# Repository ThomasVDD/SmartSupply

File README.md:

# SmartSupply
SmartSupply is a digital battery powered lab powersupply. It is Arduino compatible and can be controlled via PC over USB.

## Specifications:
 * 0 - 1A,  steps of 1 mA  (10 bit DAC)
 * 0 - 20V, steps of 20 mV (10 bit DAC) (true 0V operation)
 * Voltage measurement: 20 mV resolution (10 bit ADC)
 * Current measurement: 
      -     < 40mA:  10uA resolution (ina219)
 			< 80mA:  20uA resolution (ina219)
 			< 160mA: 40uA resolution (ina219)
			< 320mA: 80uA resolution (ina219)
			> 320mA: 1mA  resolution (10 bit ADC)

## Features: 
 * Constant voltage and constant current modes
 * Uses a low noise linear regulator, preceded by a tracking preregulator to minimize power dissipation
 * Aluminium case end panel used as heatsink 
 * Use of handsolderable components to keep the project accessible 
 * Powered by ATMEGA328P, programmed with Arduino IDE
 * PC communication via Java application over micro usb
 * Powered by 2 protected 18650 Lithium Ion cells
 * 19 mm spaced banana plugs for compatibility with BNC adapters

## Theory of operation: 

To understand the operation of the circuit, we will have to look at the schematic. I divided it into functional blocks, such that it is easier to understand; I will thus also explain the operation step by step. 

### Main block
The operation is based around the LT3080 chip: it's a linear voltage regulator, which can step down voltages, based on a control signal. This control signal will be generated by a microcontroller; how this is done, will be explained in detail later. 

#### Voltage setting
The circuitry around the LT3080 generates the appropriate control signals. First, we will take a look at how the voltage is set. 
The voltage setting from the microcontroller is a PWM signal (PWM_Vset), which is filtered by a lowpass filter (C9 & R26). This produces an analog voltage - between 0 and 5 V - proportional to the wanted output voltage. Since our output range is 0 - 20 V, we will have to amplify this signal with a factor of 4. This is done by the non inverting opamp configuration of U3C. The gain to the set pin is determined by R23//R24//R25 and R34. These resistors are 0.1% tolerant, to minimize errors. R39 and R36 don't matter here, as they are part of the feedback loop.

#### Current setting
This set pin can also be used for the second setting: current mode. We want to measure the current draw, and turn the output off when this exceeds the wanted current. Therefore, we start again by a PWM signal (PWM_Iset), generated by the microcontroller, which is now lowpass filtered and attenuated to go from a 0 - 5 V range to a 0 - 2 V range. This voltage is now compared to the voltage drop across the current sense resistor (ADC_Iout, see below) by the comparator configuration of opamp U3D. If the current is too high, this will turn on an led, and also pull the set line of the LT3080 to ground (via Q2), thus turning off the output.

The measurement of the current, and the generation of the signal ADC_Iout is done as follows. The output current flows through resistors R7 - R16. These total 1 ohm; the reason for not using 1R in the first place is twofold: 1 resistor would need to have a higher power rating (it needs to dissipate at least 1 W), and by using 10 1% resistors in parallel, we get a higher precision than with a single 1 % resistor. A good video about why this works can be found here: https://www.youtube.com/watch?v=1WAhTdWErrU&t=1s
When current flows through these resistors, it creates a voltage drop, which we can measure, and it is placed before the LT3080, since the voltage drop across it should not influence the output voltage. 
The voltage drop is measured with a differential amplifier (U3B) with a gain of 2. This results in a voltage range of 0 - 2 V (more on that later), hence the voltage divider at the PWM signal of the current. The buffer (U3A) is there to make sure that the current flowing into resistors R21, R32 and R33 is not going through the current sense resistor, which would influence it's reading. 
Also note that this should be a rail-to-rail opamp, because the input voltage at the positive input equals the supply voltage. 

The non inverting amplifier is only for the course measurement though, for very precise measurements, we have the INA219 chip on board. This chip allows us to measure very small currents, and is addressed via I2C. 

#### Additional things
At the output of the LT3080, we have some more stuff. First of all, there is a current sink (LM334). This draws a constant current of 677 uA (set by resistor R41), to stabilize the LT3080. It is however not connected to ground, but to VEE, a negative voltage. This is needed to allow the LT3080 to operate down to 0 V. When connected to ground, the lowest voltage would be about 0.7 V. This seems low enough, but keep in mind that this prevents us from turning the powersupply completely off. 
The zener diode D3 is used to clamp the output voltage if it goes above 22 V, and the resistor divider drops the output voltage range from 0 - 20 V to 0 - 2 V (ADC_Vout). 
Unfortunately, these circuits are at the output off the LT3080, which means their current will contribute to the output current we want to measure. Fortunately, these currents are constant if the voltage stays constant; so we can calibrate the current when the load is disconnected first. 

### Charge pump
The negative voltage that we mentioned before is generated by a curious little circuit: the charge pump. For it's operation, I would refer to here: https://www.youtube.com/watch?v=LtoPHevexTM&t=2s It is fed by a 50% PWM of the microcontroller (PWM)

### Boost Converter
Let's now take a look at the input voltage of our main block: Vboost. We see that it is 8 - 24V, but wait, 2 lithium cells in series gives a maximum of 8.4 V? Indeed, and that's why we need to boost the voltage, with a so called boost converter. We could always boost the voltage to 24 V, no matter what output we want; however, this would waste a lot of power in the LT3080 and things would get toasty hot! So instead of doing that, we will boost the voltage to a bit more than the output voltage. About 2.5 V higher is appropriate, to account for the voltage drop in the current sense resistor and the dropout voltage of the LT3080. 
The voltage is set by resistors on the output signal of the boost converter. To change this voltage on the fly, we use a digital potentiometer, the MCP41010, which is controlled via SPI. 

### Battery Charging
This leads us to the real input voltage: the batteries! Since we use protected cells, we simply need to put them in series and we're done! It is important to use protected cells here, to avoid overcurrent or overdischarge, and thus damaging, of the cells. 
Again, we use a voltage divider for measuring the battery voltage, and dropping it down to a usable range.
Now on to the interesting part: the charging circuitry. We use the BQ2057WSN chip for this purpose: in combination with the TIP32CG, it basically forms a linear powersupply itself. This chip charges the cells via an appropriate CV CC trajectory. Since my batteries don't have a temperature probe, this input should be tied to half the battery voltage. This concludes the voltage regulation part of the powersupply. 

### 5V regulator
The 5 V supply voltage of the arduino is made with this simple voltage regulator. It is not the most precise 5 V output however, but this will be solved below. 

### 2.048 V voltage reference
This little chip provides a very accurate 2.048 V voltage reference. This is used as a reference for the analog signals ADC_Vout, ADC_Iout, ADC_Vbatt. That's why we needed voltage dividers to bring these signals down to 2 V. 

### Microcontroller
The brain of this project is the ATMEGA328P, this is the same chip that is used in the Arduino Uno. We already went over most control signals, but there are some interesting additions nonetheless. The rotary encoders are connected to the 2 only external interrupt pins of the arduino: PD2 and PD3. This is needed for a reliable software implementation. The switches underneath use an internal pullup resistor. 
Then there is this strange voltage divider on the chip select line of the potentiometer (Pot). A voltage divider on an output, what's that good for; you might say. As mentioned before, the 5 V supply is not teribbly accurate. It would thus be good to measure this accurately, and adjust the duty cycle of the PWM signal accordingly. But since I had no more free inputs, I had to make a pin pull double duty. When the powersupply boots, this pin is first set as an input: it measures the supply rail and calibrates itself. Next, it is set as an output and it can drive the chip select line. 

### Display Driver
For the display, I wanted a commonly available - and cheap - hitachi lcd screen. They are driven by 6 pins, but since I had no pins left, I needed another solution. A shift register to the rescue! The 74HC595 allows me to use the SPI line to control the display, thus only needing 1 additional chip select line. 

### FTDI
The last part of this powersupply is the connection with the cruel, outside world. For this, we need to convert the serial signals into USB signals. This is done by an FTDI chip, which is connected to a micro USB port for easy connection.

And that's all there is to it! 

## Licensing and acknowledgements

This project would never have been possible without the help of some people, so a shootout seems appropriate.
 * This project is based on EEVBLOG's uSupply project and his Rev C schematic. So a special thanks to David L. Jones for releasing his schematics under an open source license and sharing all his knowledge.
 * A huge thanks to Johan Pattyn for producing the prototypes of this project. 
 * Also Cedric Busschots and Hans Ingelberts deserve credit for the help with troubleshooting.

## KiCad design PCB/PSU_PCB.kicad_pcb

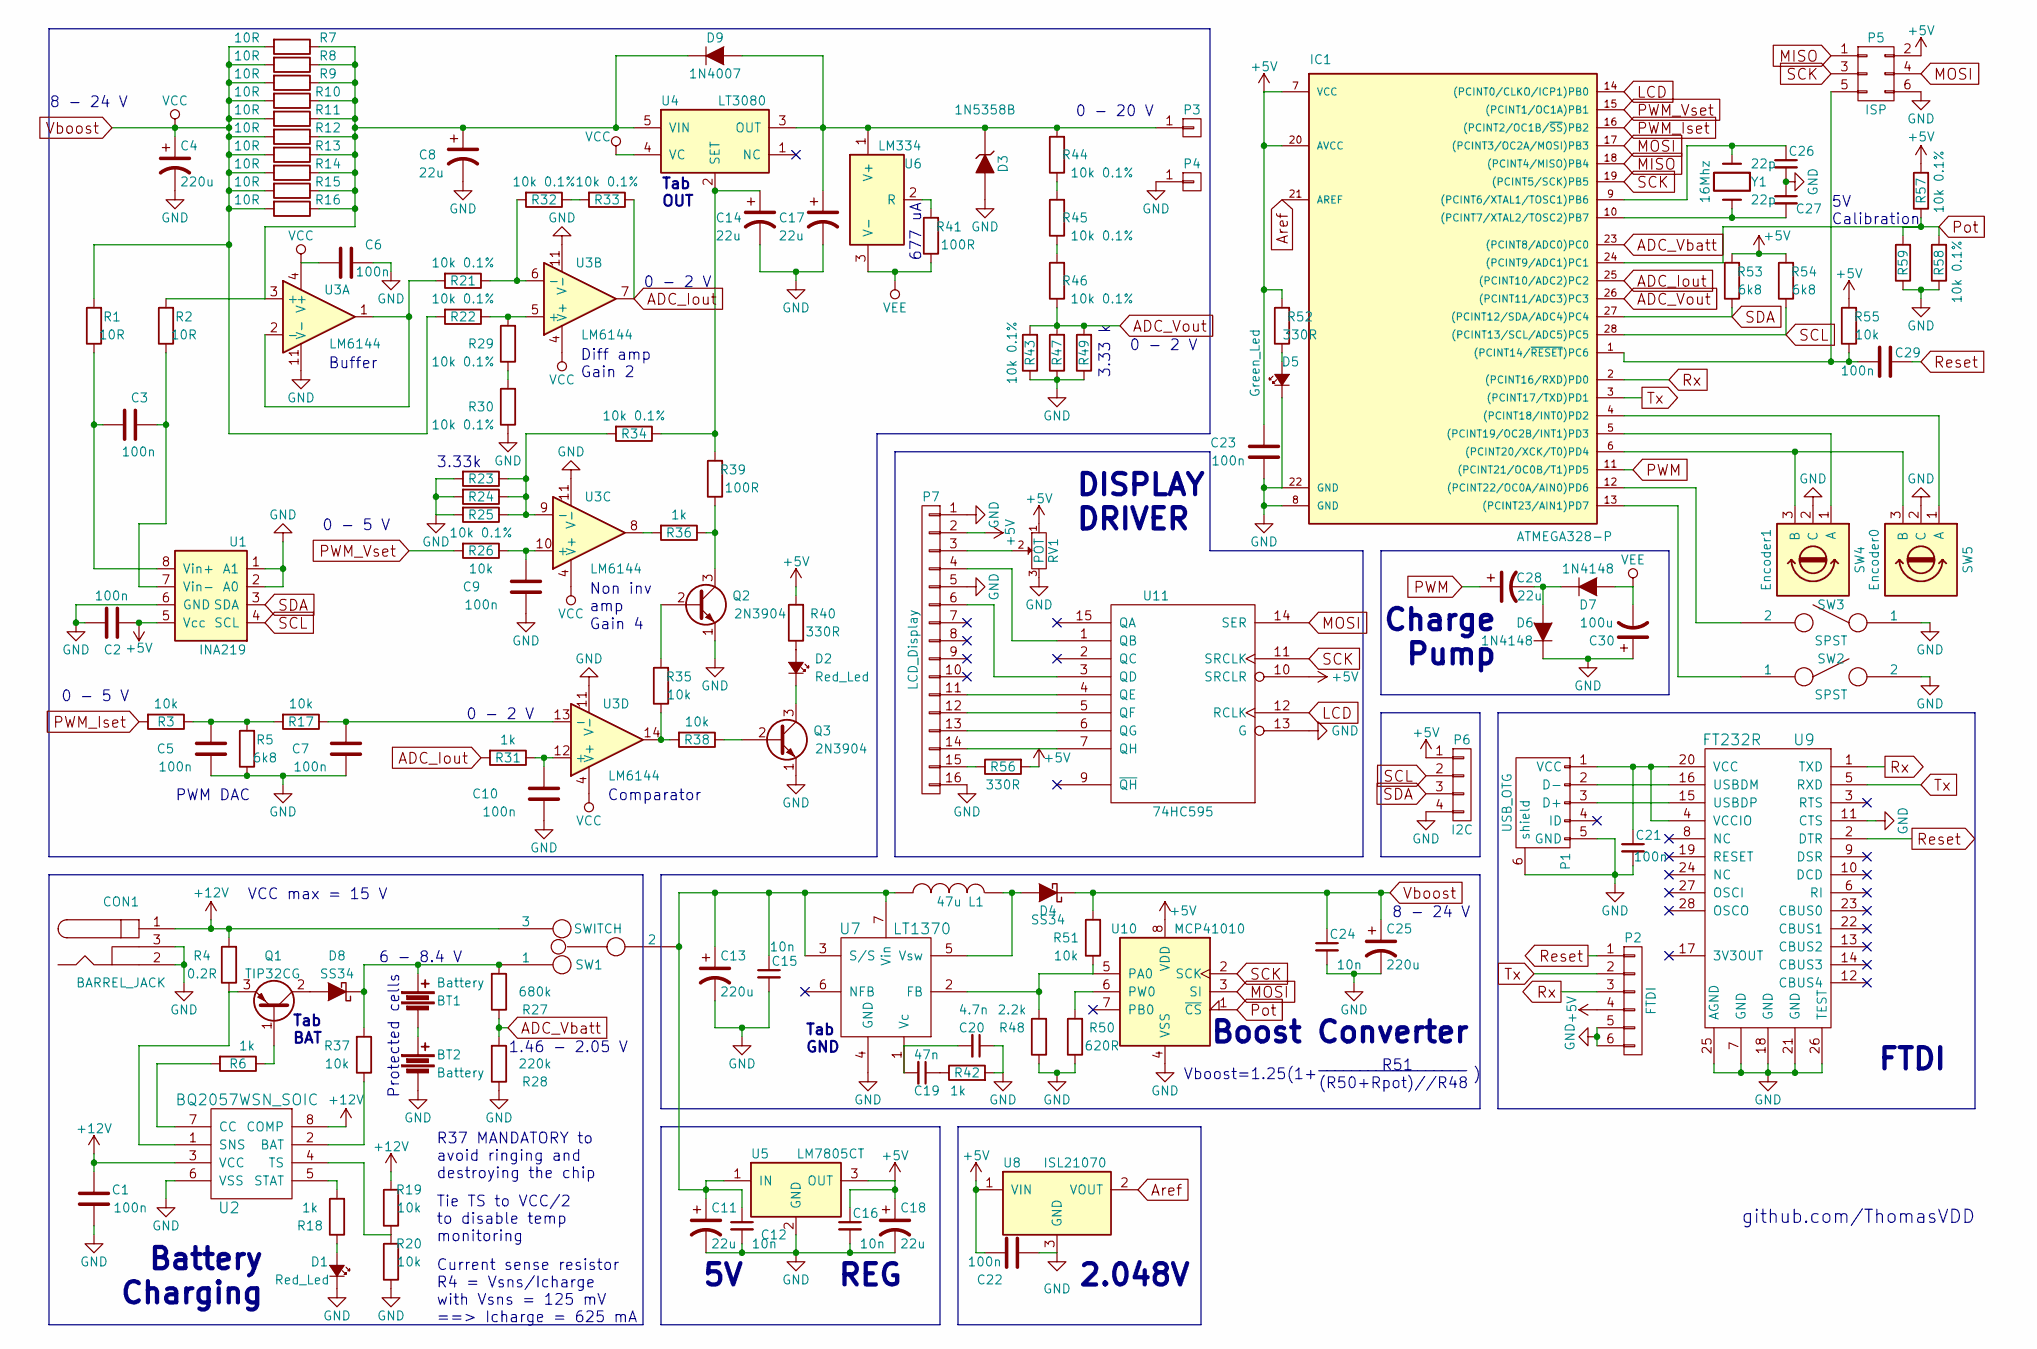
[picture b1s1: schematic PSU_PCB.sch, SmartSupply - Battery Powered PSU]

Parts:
BT1, BT2: Battery; 18650_cell
C1, C21: 100n; C_Rect_L7.0mm_W2.5mm_P5.00mm
C2, C3, C5, C6, C7, C9, C10, C22, C23, C29: 100n; C_Rect_L7_W2.5_P5
C4, C13, C25: 220u; C_Radial_D10_L13_P5
C8, C11, C14, C17, C18: 22u; C_Radial_D10_L13_P5
C12, C15, C16, C24: 10n; C_Disc_D3_P2.5
C19: 47n; C_Disc_D3.0mm_W1.6mm_P2.50mm
C20: 4.7n; C_Disc_D3.0mm_W1.6mm_P2.50mm
C26, C27: 22p; C_Disc_D3_P2.5
C28: 22u; C_Radial_D5_L11_P2.5
C30: 100u; C_Radial_D5_L11_P2.5
CON1: BARREL_JACK
D1: Red_Led; LED_D3.0mm
D2: Red_Led; LED-3MM
D3: 1N5358B; D_DO-15_P15.24mm_Horizontal
D4: SS34; SMB_Handsoldering
D5: Green_Led; LED-3MM
D6, D7: 1N4148; Diode_DO-41_SOD81_Horizontal_RM10
D8: SS34; D_SMB_Handsoldering
D9: 1N4007; D_DO-41_SOD81_P10.16mm_Horizontal
IC1: ATMEGA328-P; DIP-28_W7.62mm_LongPads
L1: 47u; SELF-WE-PD-XXL
P1: USB_OTG; Micro_usb
P2: FTDI; Pin_Header_Straight_1x06
P3: V+; 1pin
P4: V-; 1pin
P5: ISP; Pin_Header_Straight_2x03
P6: I2C; Pin_Header_Straight_1x04
P7: LCD_Display; Pin_Header_Straight_1x16
Q1: TIP32CG; TO-220_Vertical
Q2, Q3: 2N3904; TO-92_Inline_Narrow_Oval
R1, R2, R7, R8, R9, R10, R11, R12, R13, R14, R15, R16: 10R; Resistor_Horizontal_RM10mm
R3, R17, R26, R35, R38, R51, R55: 10k; Resistor_Horizontal_RM10mm
R4: 0.2R; R_0805_HandSoldering
R5, R53, R54: 6k8; Resistor_Horizontal_RM10mm
R6, R18, R42: 1k; R_Axial_DIN0207_L6.3mm_D2.5mm_P10.16mm_Horizontal
R19, R20, R37: 10k; R_Axial_DIN0207_L6.3mm_D2.5mm_P10.16mm_Horizontal
R21, R22, R25, R29, R30, R32, R33, R34, R43, R44, R45, R47: 10k 0.1%; Resistor_Horizontal_RM10mm
R23, R24, R46, R49, R57, R58, R59: 10k 0.1%; R_Axial_DIN0207_L6.3mm_D2.5mm_P10.16mm_Horizontal
R27: 680k; Resistor_Horizontal_RM10mm
R28: 220k; Resistor_Horizontal_RM10mm
R31, R36: 1k; Resistor_Horizontal_RM10mm
R39, R41: 100R; Resistor_Horizontal_RM10mm
R40, R52, R56: 330R; Resistor_Horizontal_RM10mm
R48: 2.2k; R_Axial_DIN0207_L6.3mm_D2.5mm_P10.16mm_Horizontal
R50: 620R; Resistor_Horizontal_RM10mm
RV1: POT; Potentiometer_Bourns_3296W_3-8Zoll_Inline_ScrewUp
SW1: SWITCH; SW_SPDT
SW2, SW3: SPST; SW_Tactile_SPST_Angled
SW4: Encoder1; Potentiometer_WirePads_Small
SW5: Encoder0; Potentiometer_WirePads_Small
U1: INA219; SOIC-8_3.9x4.9mm_Pitch1.27mm
U2: BQ2057WSN_SOIC; SOIC-8_3.9x4.9mm_Pitch1.27mm
U3: LM6144; DIP-14_W7.62mm_LongPads
U4: LT3080; Pentawatt_Neutral_Staggered_Verical_TO220-5-T05D
U5: LM7805CT; SOT-223-3Lead_TabPin2
U6: LM334; TO-92_Inline_Narrow_Oval
U7: LT1370; Pentawatt_Neutral_Staggered_Verical_TO220-5-T05D
U8: ISL21070; SOT-23_Handsoldering
U9: FT232R; SSOP-28_5.3x10.2mm_Pitch0.65mm
U10: MCP41010; DIP-8_W7.62mm_LongPads
U11: 74HC595; DIP-16_W7.62mm_LongPads
Y1: 16Mhz; Crystal_HC50-U_Vertical

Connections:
+5V: C2.1, C16.1, C18.1, C22.2, C23.2, IC1.7 (VCC), IC1.20 (AVCC), P2.4, P5.2, P6.1, P7.2, R40.2, R52.2, R53.2, R54.2, R55.2, R56.2, R57.2, RV1.1, U1.5 (Vcc), U5.3 (OUT), U8.1 (VIN), U10.8 (VDD), U11.10 (SRCLR), U11.16 (+5V)
+12V: C1.2, CON1.1, R4.2, R19.2, SW1.3, U2.3 (VCC), U2.8 (COMP)
ADC_Iout: IC1.25 ((PCINT10/ADC2)PC2), R31.2, R33.1, U3.7
ADC_Vbatt: IC1.23 ((PCINT8/ADC0)PC0), R27.1, R28.2
ADC_Vout: IC1.26 ((PCINT11/ADC3)PC3), R43.2, R46.1, R47.2, R49.2
Aref: IC1.21 (AREF), U8.2 (VOUT)
GND: BT2.2, C1.1, C2.2, C4.2, C5.1, C6.1, C7.1, C8.2, C9.1, C10.1, C11.2, C12.2, C13.2, C14.2, C15.2, C16.2, C17.2, C18.2, C20.1, C21.2, C22.1, C23.1, C24.2, C25.2, C26.2, C27.1, C30.1, CON1.2, CON1.3, D1.1 (K), D3.2 (A), D5.1 (K), D6.1 (K), IC1.8 (GND), IC1.22 (GND), P1.5 (GND), P1.6 (shield), P2.5, P2.6, P4.1, P5.6, P6.4, P7.1, P7.5, P7.16, Q2.1 (E), Q3.1 (E), R5.1, R20.1, R23.2, R24.2, R25.2, R28.1, R30.1, R42.2, R43.1, R47.1, R48.1, R49.1, R50.1, R58.1, R59.1, RV1.3, SW2.2, SW3.1, SW4.2 (C), SW5.2 (C), U1.1 (A1), U1.2 (A0), U1.6 (GND), U2.6 (VSS), U3.11 (V-), U5.2 (GND), U7.4 (GND), U8.3 (GND), U9.7 (GND), U9.11 (CTS), U9.18 (GND), U9.21 (GND), U9.25 (AGND), U9.26 (TEST), U10.4 (VSS), U11.8 (GND), U11.13 (G)
LCD: IC1.14 ((PCINT0/CLKO/ICP1)PB0), U11.12 (RCLK)
MISO: IC1.18 ((PCINT4/MISO)PB4), P5.1
MOSI: IC1.17 ((PCINT3/OC2A/MOSI)PB3), P5.4, U10.3 (SI), U11.14 (SER)
unnamed: BT1.1, D8.1 (K), R27.2, R37.2, SW1.1
unnamed: BT1.2, BT2.1
unnamed: C3.1, R2.1, U1.7 (Vin-)
unnamed: C3.2, R1.1, U1.8 (Vin+)
unnamed: C5.2, R3.1, R5.2, R17.2
unnamed: C7.2, R17.1, U3.13 (-)
unnamed: C8.1, D9.1 (K), R2.2, R7.1, R8.1, R9.1, R10.1, R11.1, R12.1, R13.1, R14.1, R15.1, R16.1, U3.3 (+), U4.5 (VIN)
unnamed: C9.2, R26.1, U3.10 (+)
unnamed: C10.2, R31.1, U3.12 (+)
unnamed: C11.1, C12.1, C13.1, C15.1, L1.2, SW1.2, U5.1 (IN), U7.3 (S/S), U7.7 (Vin)
unnamed: C14.1, R34.1, R39.2, U4.2 (SET)
unnamed: C17.1, D3.1 (K), D9.2 (A), P3.1, R44.2, U4.3 (OUT), U6.1 (V+)
unnamed: C19.1, R42.1
unnamed: C19.2, C20.2, U7.1 (Vc)
unnamed: C21.1, P1.1 (VCC), U9.4 (VCCIO), U9.20 (VCC)
unnamed: C26.1, IC1.9 ((PCINT6/XTAL1/TOSC1)PB6), Y1.1
unnamed: C27.2, IC1.10 ((PCINT7/XTAL2/TOSC2)PB7), Y1.2
unnamed: C28.2, D6.2 (A), D7.1 (K)
unnamed: C29.2, IC1.1 ((PCINT14/~RESET~)PC6), P5.5, R55.1
unnamed: D1.2 (A), R18.1
unnamed: D2.1 (K), Q3.3 (C)
unnamed: D2.2 (A), R40.1
unnamed: D4.2 (A), L1.1, U7.5 (Vsw)
unnamed: D5.2 (A), R52.1
unnamed: D8.2 (A), Q1.2 (C)
unnamed: IC1.4 ((PCINT18/INT0)PD2), SW5.1 (A)
unnamed: IC1.5 ((PCINT19/OC2B/INT1)PD3), SW4.1 (A)
unnamed: IC1.6 ((PCINT20/XCK/T0)PD4), SW4.3 (B), SW5.3 (B)
unnamed: IC1.12 ((PCINT22/OC0A/AIN0)PD6), SW3.2
unnamed: IC1.13 ((PCINT23/AIN1)PD7), SW2.1
unnamed: P1.2 (D-), U9.16 (USBDM)
unnamed: P1.3 (D+), U9.15 (USBDP)
unnamed: P7.3, RV1.2
unnamed: P7.4, U11.1 (QB)
unnamed: P7.6, U11.3 (QD)
unnamed: P7.11, U11.4 (QE)
unnamed: P7.12, U11.5 (QF)
unnamed: P7.13, U11.6 (QG)
unnamed: P7.14, U11.7 (QH)
unnamed: P7.15, R56.1
unnamed: Q1.1 (B), R6.1
unnamed: Q1.3 (E), R4.1, U2.1 (SNS)
unnamed: Q2.2 (B), R35.2
unnamed: Q2.3 (C), R36.1, R39.1
unnamed: Q3.2 (B), R38.1
unnamed: R6.2, U2.7 (CC)
unnamed: R18.2, U2.5 (STAT)
unnamed: R19.1, R20.2, U2.4 (TS)
unnamed: R21.1, R32.2, U3.6 (-)
unnamed: R21.2, U3.1, U3.2 (-)
unnamed: R22.1, R29.2, U3.5 (+)
unnamed: R23.1, R24.1, R25.1, R34.2, U3.9 (-)
unnamed: R29.1, R30.2
unnamed: R32.1, R33.2
unnamed: R35.1, R38.2, U3.14
unnamed: R36.2, U3.8
unnamed: R37.1, U2.2 (BAT)
unnamed: R41.2, U6.2 (R)
unnamed: R44.1, R45.2
unnamed: R45.1, R46.2
unnamed: R48.2, R51.1, U7.2 (FB), U10.5 (PA0)
unnamed: R50.2, U10.6 (PW0)
PWM: C28.1, IC1.11 ((PCINT21/OC0B/T1)PD5)
PWM_Iset: IC1.16 ((PCINT2/OC1B/~SS~)PB2), R3.2
PWM_Vset: IC1.15 ((PCINT1/OC1A)PB1), R26.2
Pot: IC1.24 ((PCINT9/ADC1)PC1), R57.1, R58.2, R59.2, U10.1 (~CS)
Reset: C29.1, P2.1, U9.2 (DTR)
Rx: IC1.2 ((PCINT16/RXD)PD0), P2.3, U9.1 (TXD)
SCK: IC1.19 ((PCINT5/SCK)PB5), P5.3, U10.2 (SCK), U11.11 (SRCLK)
SCL: IC1.28 ((PCINT13/SCL/ADC5)PC5), P6.2, R54.1, U1.4 (SCL)
SDA: IC1.27 ((PCINT12/SDA/ADC4)PC4), P6.3, R53.1, U1.3 (SDA)
Tx: IC1.3 ((PCINT17/TXD)PD1), P2.2, U9.5 (RXD)
VEE: C30.2, D7.2 (A), R41.1, U6.3 (V-)
Vboost: C4.1, C6.2, C24.1, C25.1, D4.1 (K), R1.2, R7.2, R8.2, R9.2, R10.2, R11.2, R12.2, R13.2, R14.2, R15.2, R16.2, R22.2, R51.2, U3.4 (V+), U4.4 (VC)

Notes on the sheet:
Current sense resistor R4 = Vsns/Icharge with Vsns = 125 mV ==> Icharge = 625 mA
6 - 8.4 V
1.46 - 2.05 V
677 uA
FTDI
DISPLAY DRIVER
Charge Pump
Battery Charging
Protected cells
5V REG
0 - 5 V
0 - 2 V
Buffer
Diff amp Gain 2
Comparator
PWM DAC
Non inv amp
Gain 4
3.33k
0 - 20 V
8 - 24 V
2.048V
3.33 k
8 - 24 V
Boost Converter
Tie TS to VCC/2 to disable temp monitoring
Tab GND
Tab OUT
github.com/ThomasVDD
Tab BAT
Vboost=1.25(1+ )
R51
(R50+Rpot)//R48
__________________
5V Calibration
R37 MANDATORY to avoid ringing and destroying the chip
VCC max = 15 V

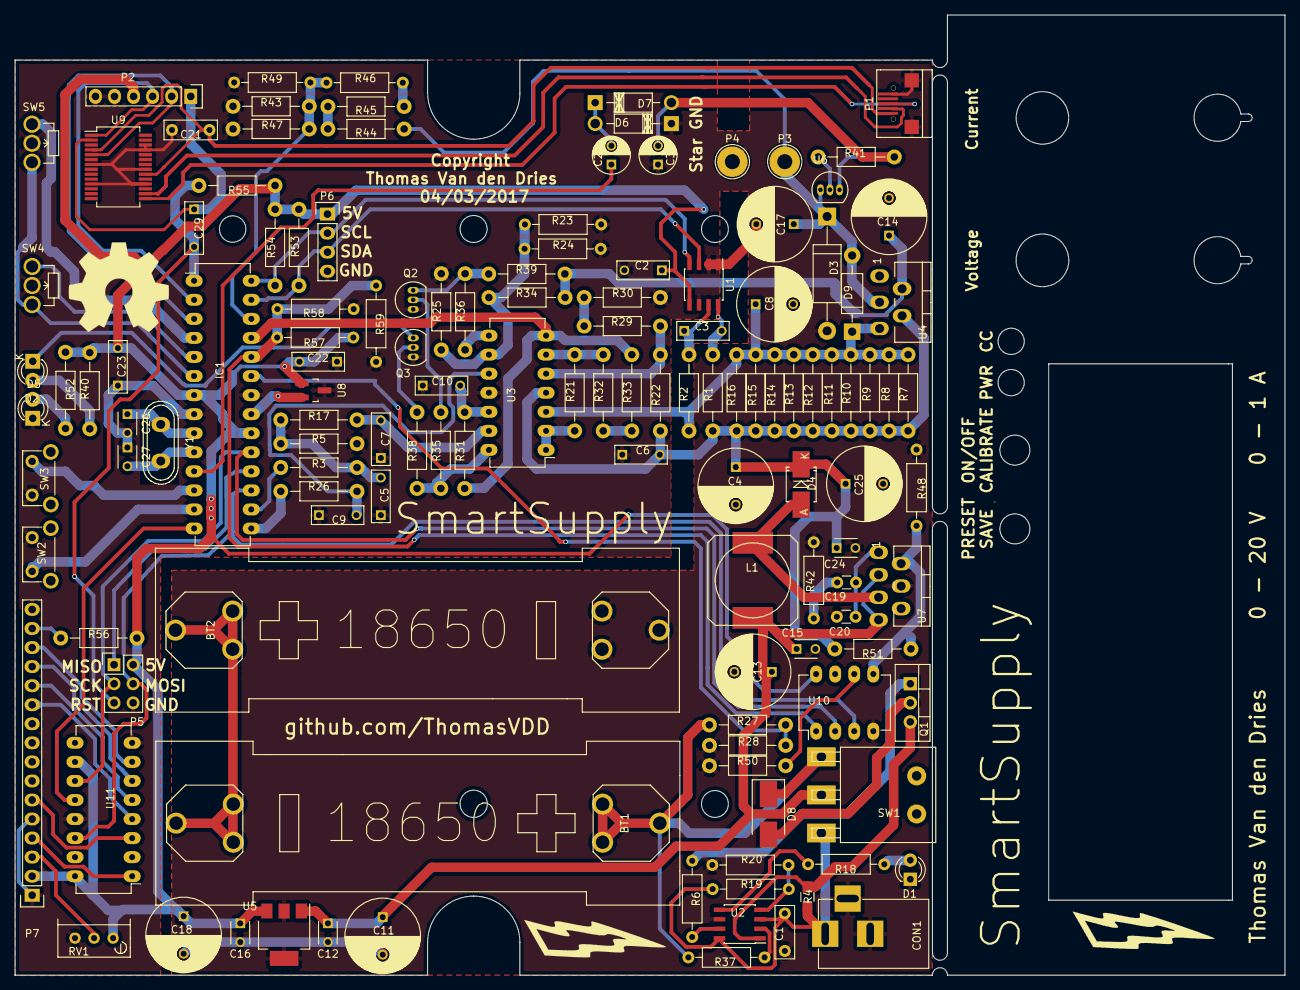
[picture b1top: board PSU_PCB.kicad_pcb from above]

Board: 2 copper layers, 169.3 x 128.0 mm, 131 parts (0 on the bottom side), 84 nets.

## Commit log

2017-03-30 Added PDFs
2017-03-31 Fixed typo in license file
2017-04-07 Changed Arduino and Java code to work with 20V instead of 10V
2017-04-08 Small schematic fixes + added backpanel design
2017-04-08 Code adapted for 20V version
2017-04-08 Deleted unnecessary files
2017-04-08 Updated changes
2017-04-08 Added welcome message
2017-04-09 Updated BOM
2017-04-09 Added comments to the code
2017-04-09 Included specifications and features of the project
2017-04-10 Adding pictures for the wiki page
2017-04-10 Added calibration for the 5V voltage regulator
2017-04-12 Added pictures
2017-04-13 Changed battery monitor resistors
2017-04-14 Added auto calibration
2017-04-14 Added autocalibration resistors
2017-04-14 Merged specifications into readme
2017-04-14 Merged acknowledgements into readme
2017-04-14 Fixed typo
2017-04-16 Change in startup sequence
2017-04-17 added oshw logo
2017-04-17 Update README.md
    Added OSHW and CC logo
2017-04-17 Added theory of operation
2017-04-17 Added resistor tolerance
2017-04-22 Small fix
2017-05-08 Added protection resistor to charging circuitry
2017-05-16 Added aliexpress prices
2017-05-25 Small BOM optimisation
2017-05-26 Esthetic change
2017-12-19 Updated INA219 library

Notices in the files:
PCB/PSU_PCB.sch:
Copyright Thomas Van den Dries 2017
